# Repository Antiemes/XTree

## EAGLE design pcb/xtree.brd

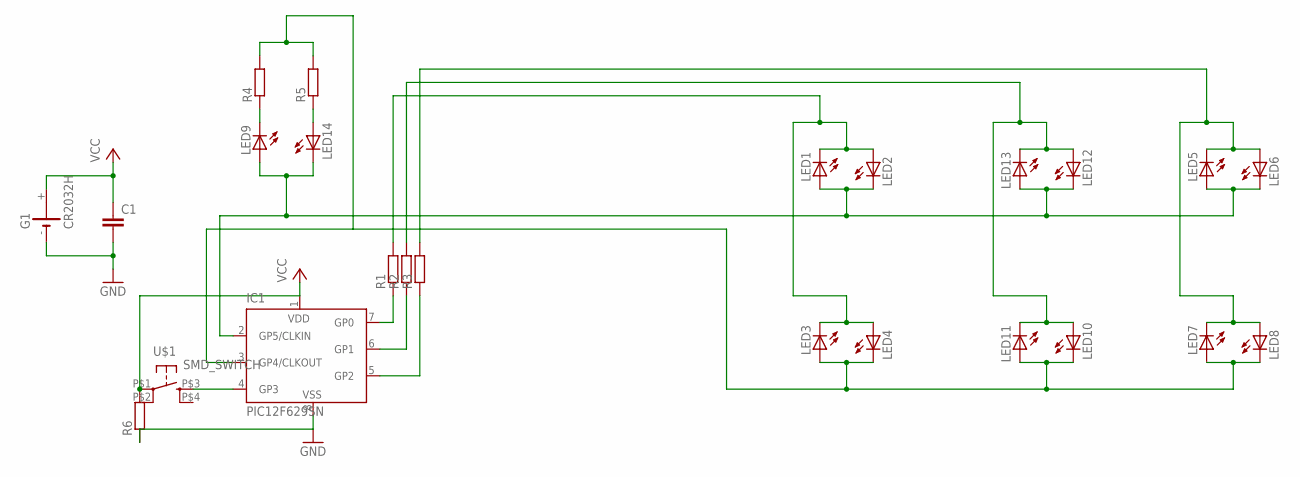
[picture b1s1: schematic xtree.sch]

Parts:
C1: C-EUC1206K; C1206K
G1: CR2032H
IC1: PIC12F629SN; SO-08
LED1, LED2, LED3, LED4, LED5, LED6, LED7, LED8, LED9, LED10, LED11, LED12, LED13, LED14: LED_E; LED_1206
R1, R2, R3, R4, R5, R6: R-EU_R0603; R0603
U$1: SMD_SWITCH; SMD_BUTTON

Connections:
GND: C1.2, G1.-, IC1.8 (VSS), R6.1
unnamed: LED1.C, LED2.A, LED3.C, LED4.A, R1.2
unnamed: IC1.3 (GP4/CLKOUT), LED3.A, LED4.C, LED7.A, LED8.C, LED10.C, LED11.A, R4.2, R5.2
unnamed: IC1.7 (GP0), R1.1
unnamed: LED5.C, LED6.A, LED7.C, LED8.A, R3.2
unnamed: LED10.A, LED11.C, LED12.A, LED13.C, R2.2
unnamed: IC1.2 (GP5/CLKIN), LED1.A, LED2.C, LED5.A, LED6.C, LED9.A, LED12.C, LED13.A, LED14.C
unnamed: IC1.6 (GP1), R2.1
unnamed: IC1.5 (GP2), R3.1
unnamed: IC1.4 (GP3), U$1.P$3 (S)
unnamed: LED9.C, R4.1
unnamed: LED14.A, R5.1
VCC: C1.1, G1.+, IC1.1 (VDD), R6.2, U$1.P$1

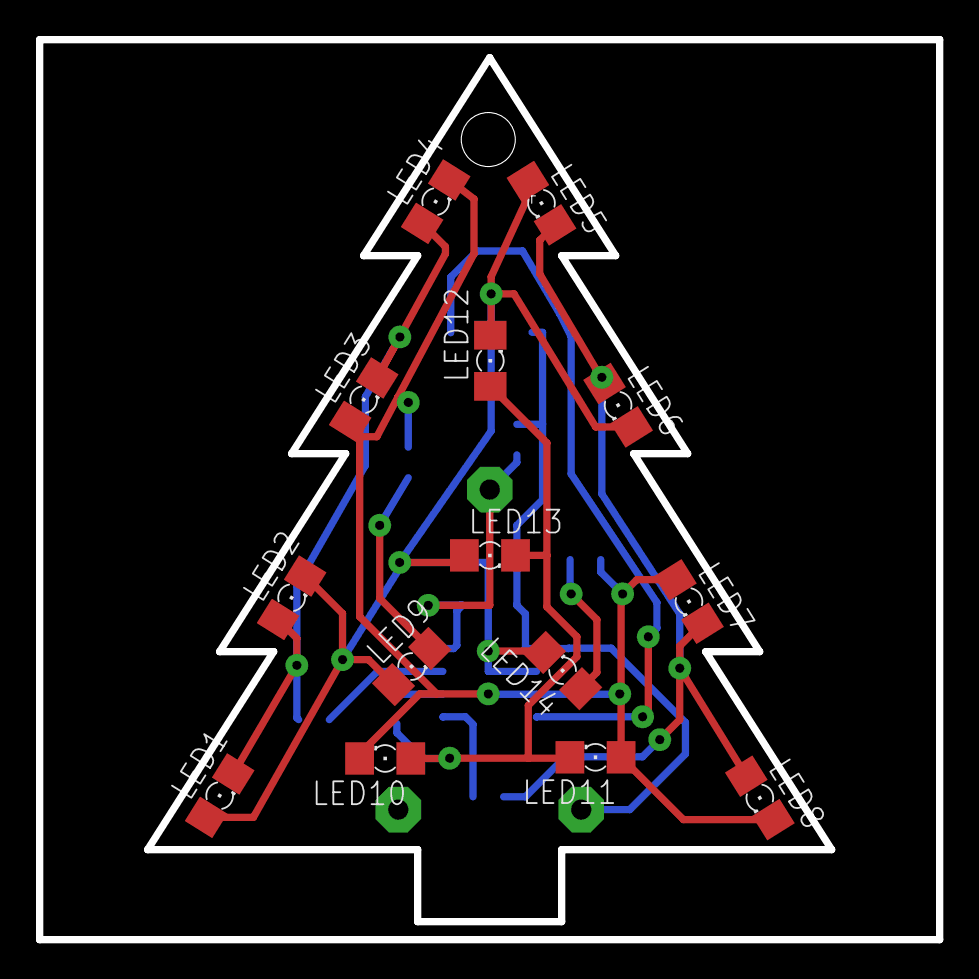
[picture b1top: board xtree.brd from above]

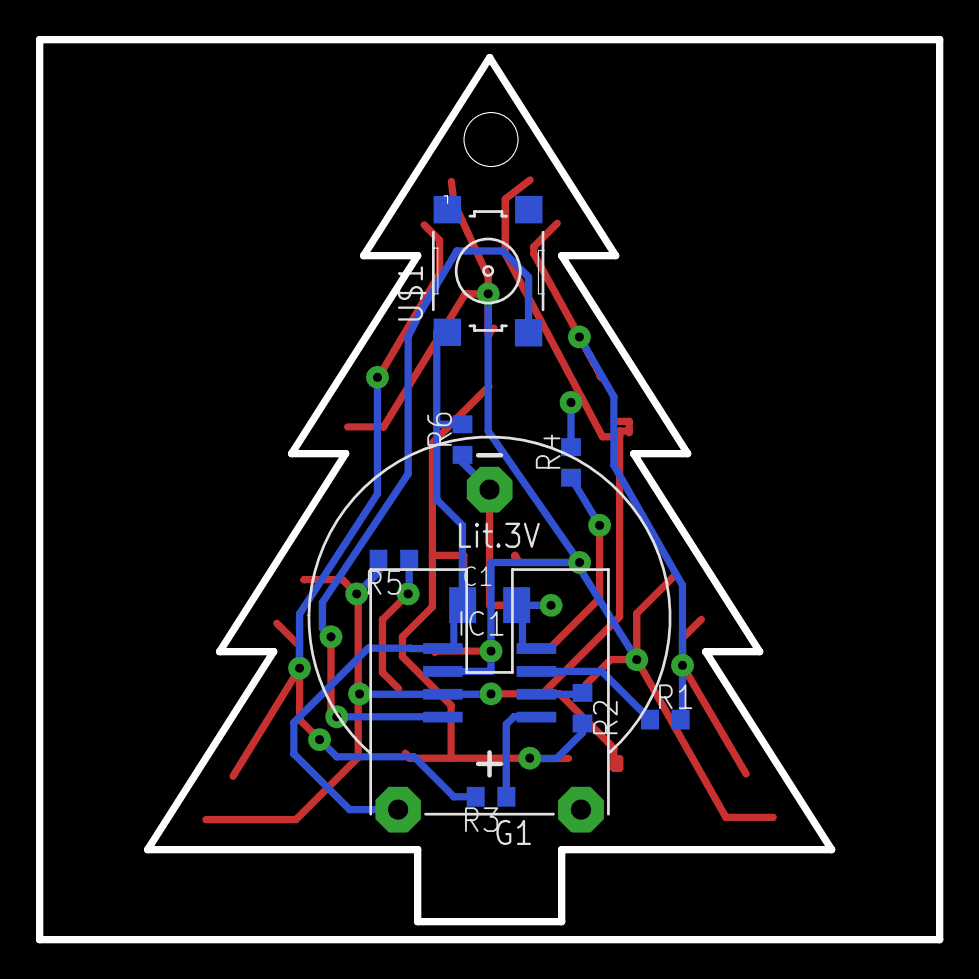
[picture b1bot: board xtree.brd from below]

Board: 2 copper layers, 50.0 x 50.0 mm, 24 parts (10 on the bottom side), 13 nets.
